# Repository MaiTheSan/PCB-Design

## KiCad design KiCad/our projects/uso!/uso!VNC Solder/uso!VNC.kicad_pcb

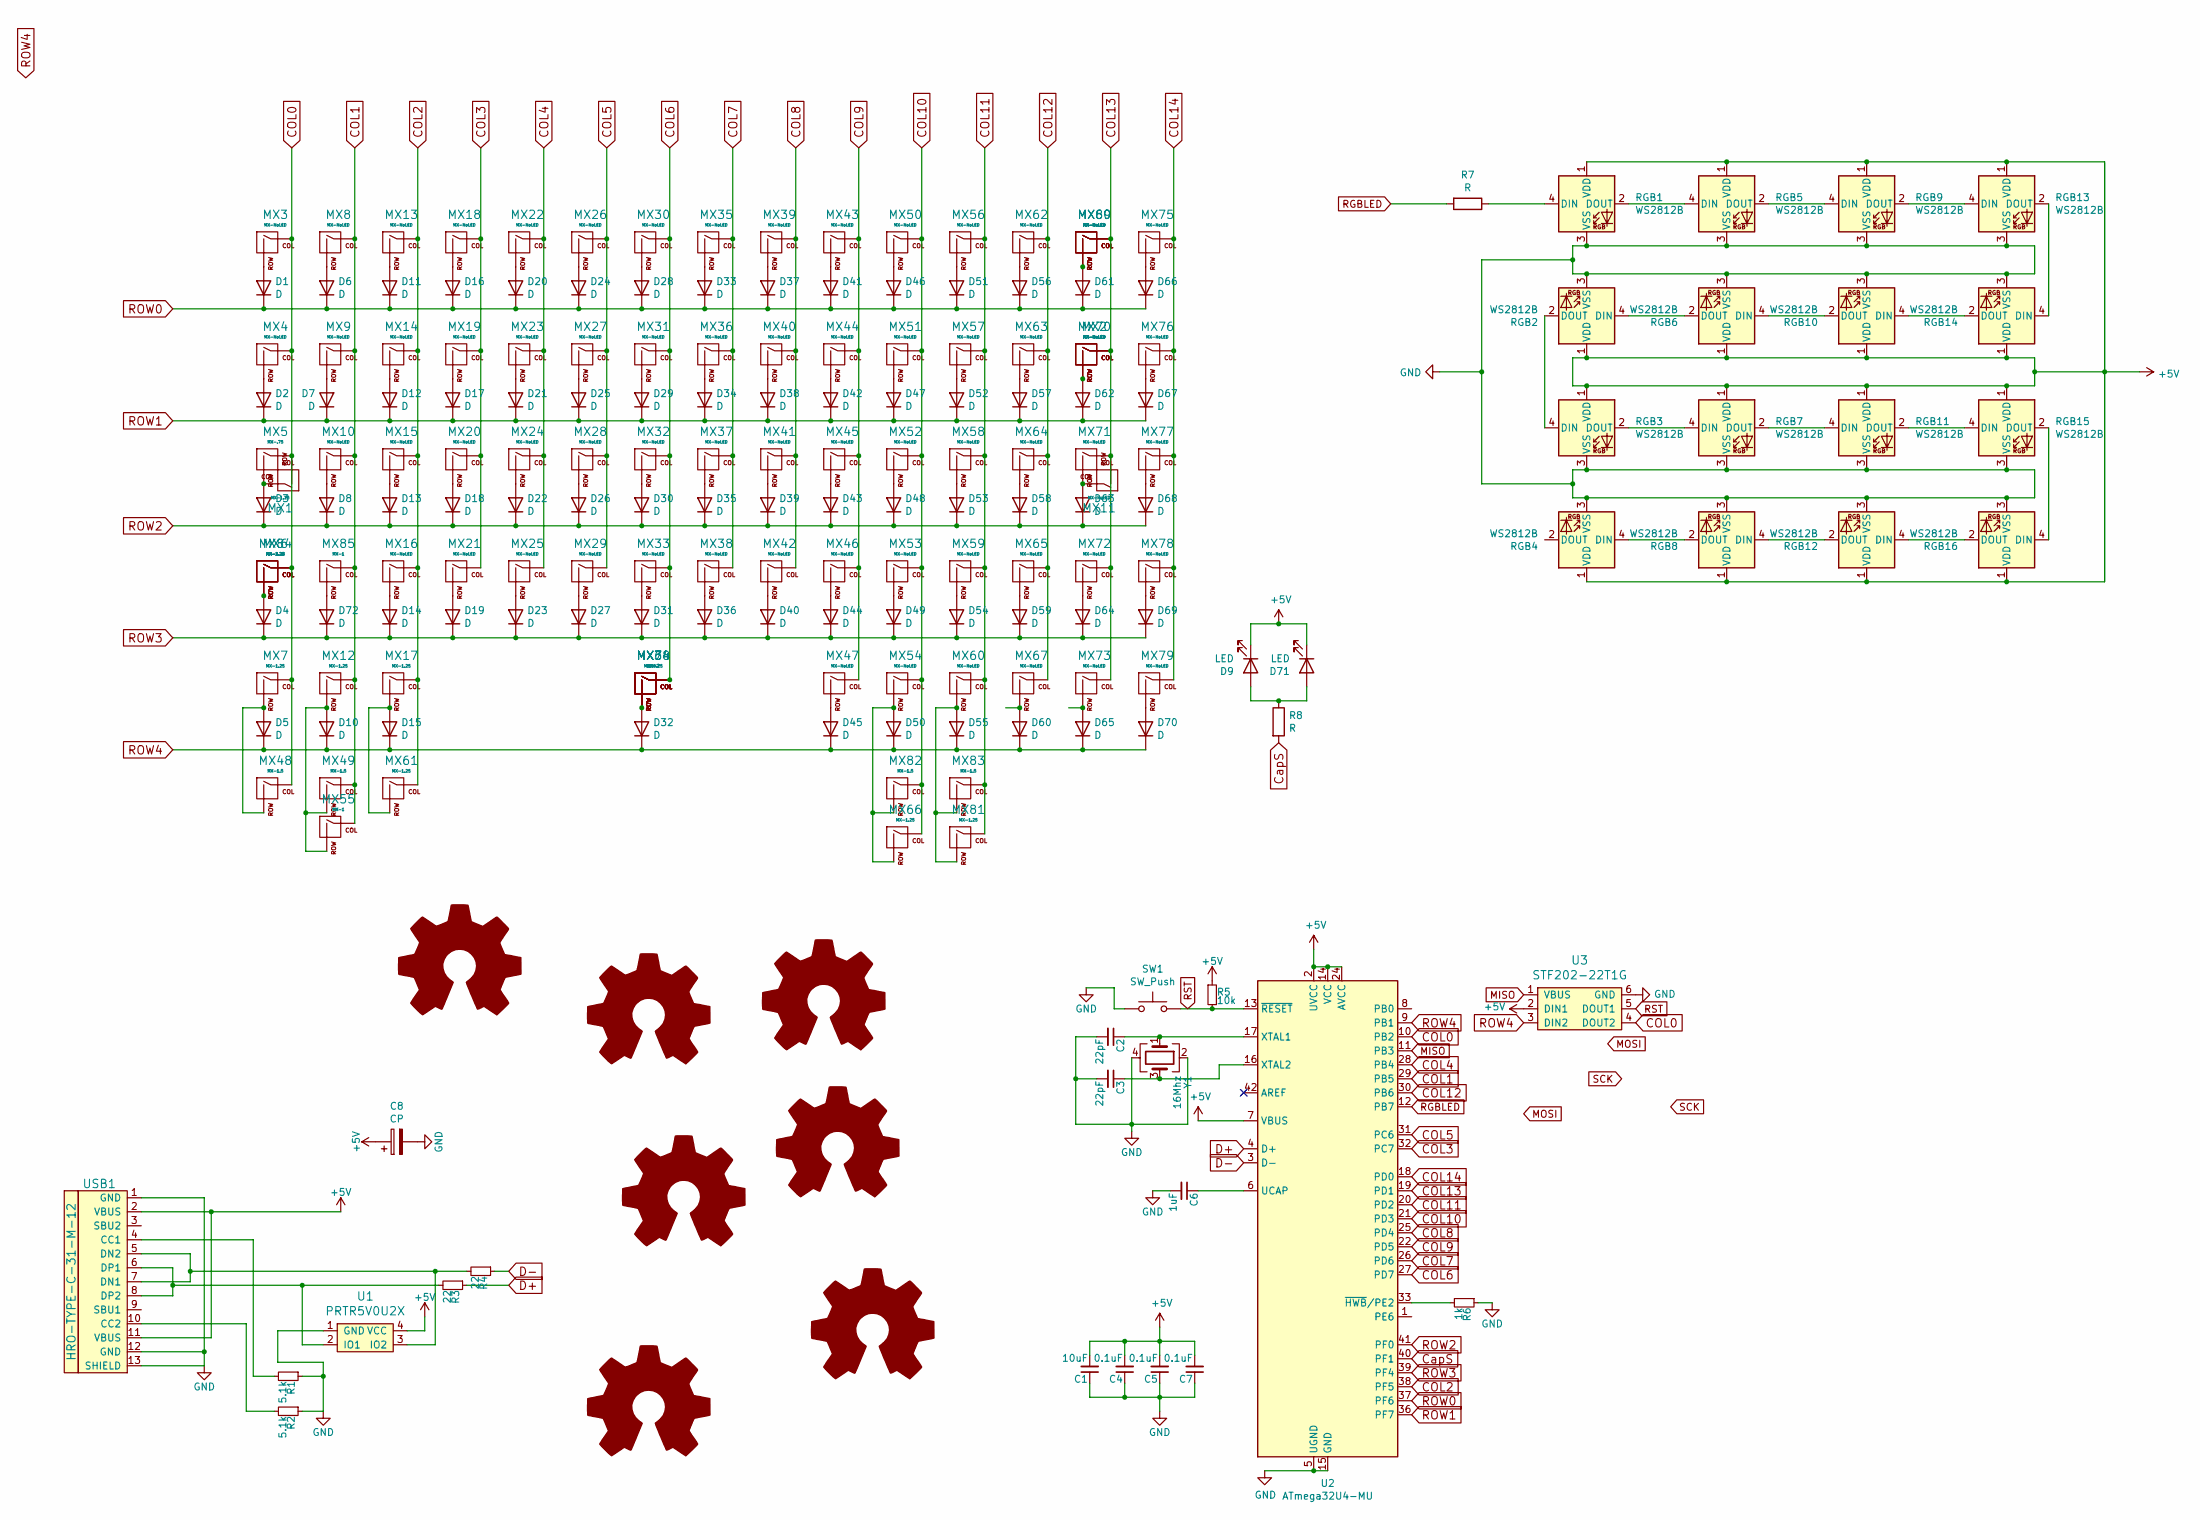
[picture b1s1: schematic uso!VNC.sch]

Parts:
C1: 10uF; C_0603
C2, C3: 22pF; C_0603
C4, C5, C7: 0.1uF; C_0603
C6: 1uF; C_0603
C8: CP; CP_EIA-3216
D1, D2, D3, D4, D5, D6, D7, D8, D10, D11, D12, D13, D14, D15, D16, D17, D18, D19, D20, D21, D22, D23, D24, D25, D26, D27, D28, D29, D30, D31, D32, D33, D34, D35, D36, D37, D38, D39, D40, D41, D42, D43, D44, D45, D46, D47, D48, D49, D50, D51, D52, D53, D54, D55, D56, D57, D58, D59, D60, D61, D62, D63, D64, D65, D66, D67, D68, D69, D70, D72: D; D_SOD-123
D9: LED; MXOnly-LEDONLY-FLIPPED
D71: LED; MXOnly-LEDONLY
LOGO1: Logo_Open_Hardware_Large; sanpjxlogo-PCB-type
LOGO2: Logo_Open_Hardware_Large; mounting-circular
LOGO3, LOGO4, LOGO5, LOGO6, LOGO7: Logo_Open_Hardware_Large; mounting-elipse
MX1, MX7, MX12, MX17, MX61, MX66, MX81, MX84: MX-1.25; MXOnly-1.25U-NoLED
MX2, MX3, MX8, MX9, MX10, MX13, MX14, MX15, MX16, MX18, MX19, MX20, MX21, MX22, MX23, MX24, MX25, MX26, MX27, MX28, MX29, MX30, MX31, MX32, MX33, MX35, MX36, MX37, MX38, MX39, MX40, MX41, MX42, MX43, MX44, MX45, MX46, MX47, MX50, MX51, MX52, MX53, MX54, MX56, MX57, MX58, MX59, MX60, MX62, MX63, MX64, MX67, MX69, MX72, MX73, MX75, MX76, MX77, MX78, MX79: MX-NoLED; MXOnly-1U-NoLED
MX4, MX70: MX-NoLED; MXOnly-1.5U-NoLED
MX5: MX-.75; MXOnly-1.75U-NoLED
MX6: MX-2.25; MXOnly-2.25U-NoLED
MX11: MX-NoLED; MXOnly-ISO-ROTATED-ReversedStabilizers-NoLED
MX34: MX-6.25; MXOnly-6.25U-ReversedStabilizers-NoLED
MX48, MX49, MX82, MX83: MX-1.5; MXOnly-1.5U-NoLED
MX55, MX85: MX-1; MXOnly-1U-NoLED
MX65: MX-NoLED; MXOnly-1.75U-NoLED
MX68, MX74: MX-7; MXOnly-7U-ReversedStabilizers-NoLED
MX71: MX-NoLED; MXOnly-2.25U-NoLED
MX80: MX-NoLED; MXOnly-2U-NoLED
R1, R2: 5.1k; R_0805
R3, R4: 22; R_0805
R5: 10k; R_0805
R6: 1k; R_0805
R7, R8: R; R_0805
RGB1, RGB2, RGB3, RGB4, RGB5, RGB6, RGB7, RGB8, RGB9, RGB10, RGB11, RGB12, RGB13, RGB14, RGB15, RGB16: WS2812B; LED_WS2812B_PLCC4_5.0x5.0mm_P3.2mm
SW1: SW_Push; SKQG-1155865
U1: PRTR5V0U2X; SOT143B
U2: ATmega32U4-MU; QFN-44-1EP_7x7mm_P0.5mm_EP5.2x5.2mm_ThermalVias
U3: STF202-22T1G; vcl65-debuger
USB1: HRO-TYPE-C-31-M-12; HRO-TYPE-C-31-M-12-Assembly
Y1: 16Mhz; Crystal_SMD_3225-4Pin_3.2x2.5mm

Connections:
+5V: C1.2, C4.2, C5.2, C7.2, C8.1, D9.1 (K), D71.1 (K), R5.1, RGB1.1 (VDD), RGB2.1 (VDD), RGB3.1 (VDD), RGB4.1 (VDD), RGB5.1 (VDD), RGB6.1 (VDD), RGB7.1 (VDD), RGB8.1 (VDD), RGB9.1 (VDD), RGB10.1 (VDD), RGB11.1 (VDD), RGB12.1 (VDD), RGB13.1 (VDD), RGB14.1 (VDD), RGB15.1 (VDD), RGB16.1 (VDD), U1.4 (VCC), U2.2 (UVCC), U2.7 (VBUS), U2.14 (VCC), U2.24 (AVCC), U2.34 (VCC), U2.44 (AVCC), U3.2 (DIN1), USB1.2 (VBUS), USB1.11 (VBUS)
COL0: MX1.2 (ROW), MX3.1 (COL), MX4.1 (COL), MX5.1 (COL), MX6.1 (COL), MX7.1 (COL), MX48.1 (COL), MX84.1 (COL), U2.10 (PB2), U3.4 (DOUT2)
COL1: MX8.1 (COL), MX9.1 (COL), MX10.1 (COL), MX12.1 (COL), MX49.1 (COL), MX55.1 (COL), MX85.1 (COL), U2.29 (PB5)
COL2: MX13.1 (COL), MX14.1 (COL), MX15.1 (COL), MX16.1 (COL), MX17.1 (COL), MX61.1 (COL), U2.38 (PF5)
COL3: MX18.1 (COL), MX19.1 (COL), MX20.1 (COL), MX21.1 (COL), U2.32 (PC7)
COL4: MX22.1 (COL), MX23.1 (COL), MX24.1 (COL), MX25.1 (COL), U2.28 (PB4)
COL5: MX26.1 (COL), MX27.1 (COL), MX28.1 (COL), MX29.1 (COL), U2.31 (PC6)
COL6: MX30.1 (COL), MX31.1 (COL), MX32.1 (COL), MX33.1 (COL), MX34.1 (COL), MX68.1 (COL), MX74.1 (COL), U2.27 (PD7)
COL7: MX35.1 (COL), MX36.1 (COL), MX37.1 (COL), MX38.1 (COL), U2.26 (PD6)
COL8: MX39.1 (COL), MX40.1 (COL), MX41.1 (COL), MX42.1 (COL), U2.25 (PD4)
COL9: MX43.1 (COL), MX44.1 (COL), MX45.1 (COL), MX46.1 (COL), MX47.1 (COL), U2.22 (PD5)
COL10: MX50.1 (COL), MX51.1 (COL), MX52.1 (COL), MX53.1 (COL), MX54.1 (COL), MX66.1 (COL), MX82.1 (COL), U2.21 (PD3)
COL11: MX56.1 (COL), MX57.1 (COL), MX58.1 (COL), MX59.1 (COL), MX60.1 (COL), MX81.1 (COL), MX83.1 (COL), U2.20 (PD2)
COL12: MX62.1 (COL), MX63.1 (COL), MX64.1 (COL), MX65.1 (COL), MX67.1 (COL), U2.30 (PB6)
COL13: MX2.1 (COL), MX11.2 (ROW), MX69.1 (COL), MX70.1 (COL), MX71.1 (COL), MX72.1 (COL), MX73.1 (COL), MX80.1 (COL), U2.19 (PD1)
COL14: MX75.1 (COL), MX76.1 (COL), MX77.1 (COL), MX78.1 (COL), MX79.1 (COL), U2.18 (PD0)
CapS: R8.2, U2.40 (PF1)
D+: R3.1, U2.4 (D+)
D-: R4.1, U2.3 (D-)
GND: C1.1, C2.2, C3.2, C4.1, C5.1, C6.2, C7.1, C8.2, R1.1, R2.1, R6.1, RGB1.3 (VSS), RGB2.3 (VSS), RGB3.3 (VSS), RGB4.3 (VSS), RGB5.3 (VSS), RGB6.3 (VSS), RGB7.3 (VSS), RGB8.3 (VSS), RGB9.3 (VSS), RGB10.3 (VSS), RGB11.3 (VSS), RGB12.3 (VSS), RGB13.3 (VSS), RGB14.3 (VSS), RGB15.3 (VSS), RGB16.3 (VSS), SW1.1, U1.1 (GND), U2.5 (UGND), U2.15 (GND), U2.23 (GND), U2.35 (GND), U2.43 (GND), U2.45 (GND), U3.6 (GND), USB1.1 (GND), USB1.12 (GND), USB1.13 (SHIELD), Y1.2, Y1.4
MISO: U2.11 (PB3), U3.1 (VBUS)
unnamed: C2.1, U2.17 (XTAL1), Y1.1
unnamed: C3.1, U2.16 (XTAL2), Y1.3
unnamed: C6.1, U2.6 (UCAP)
unnamed: D1.2 (A), MX3.2 (ROW)
unnamed: D2.2 (A), MX4.2 (ROW)
unnamed: D3.2 (A), MX1.1 (COL), MX5.2 (ROW)
unnamed: D4.2 (A), MX6.2 (ROW), MX84.2 (ROW)
unnamed: D5.2 (A), MX7.2 (ROW), MX48.2 (ROW)
unnamed: D6.2 (A), MX8.2 (ROW)
unnamed: D7.2 (A), MX9.2 (ROW)
unnamed: D8.2 (A), MX10.2 (ROW)
unnamed: D10.2 (A), MX12.2 (ROW), MX49.2 (ROW), MX55.2 (ROW)
unnamed: D11.2 (A), MX13.2 (ROW)
unnamed: D12.2 (A), MX14.2 (ROW)
unnamed: D13.2 (A), MX15.2 (ROW)
unnamed: D14.2 (A), MX16.2 (ROW)
unnamed: D15.2 (A), MX17.2 (ROW), MX61.2 (ROW)
unnamed: D16.2 (A), MX18.2 (ROW)
unnamed: D17.2 (A), MX19.2 (ROW)
unnamed: D18.2 (A), MX20.2 (ROW)
unnamed: D19.2 (A), MX21.2 (ROW)
unnamed: D20.2 (A), MX22.2 (ROW)
unnamed: D21.2 (A), MX23.2 (ROW)
unnamed: D22.2 (A), MX24.2 (ROW)
unnamed: D23.2 (A), MX25.2 (ROW)
unnamed: D24.2 (A), MX26.2 (ROW)
unnamed: D25.2 (A), MX27.2 (ROW)
unnamed: D26.2 (A), MX28.2 (ROW)
unnamed: D27.2 (A), MX29.2 (ROW)
unnamed: D28.2 (A), MX30.2 (ROW)
unnamed: D29.2 (A), MX31.2 (ROW)
unnamed: D30.2 (A), MX32.2 (ROW)
unnamed: D31.2 (A), MX33.2 (ROW)
unnamed: D32.2 (A), MX34.2 (ROW), MX68.2 (ROW), MX74.2 (ROW)
unnamed: D33.2 (A), MX35.2 (ROW)
unnamed: D34.2 (A), MX36.2 (ROW)
unnamed: D35.2 (A), MX37.2 (ROW)
unnamed: D36.2 (A), MX38.2 (ROW)
unnamed: D37.2 (A), MX39.2 (ROW)
unnamed: D38.2 (A), MX40.2 (ROW)
unnamed: D39.2 (A), MX41.2 (ROW)
unnamed: D40.2 (A), MX42.2 (ROW)
unnamed: D41.2 (A), MX43.2 (ROW)
unnamed: D42.2 (A), MX44.2 (ROW)
unnamed: D43.2 (A), MX45.2 (ROW)
unnamed: D44.2 (A), MX46.2 (ROW)
unnamed: D45.2 (A), MX47.2 (ROW)
unnamed: D46.2 (A), MX50.2 (ROW)
unnamed: D47.2 (A), MX51.2 (ROW)
unnamed: D48.2 (A), MX52.2 (ROW)
unnamed: D49.2 (A), MX53.2 (ROW)
unnamed: D50.2 (A), MX54.2 (ROW), MX66.2 (ROW), MX82.2 (ROW)
unnamed: D51.2 (A), MX56.2 (ROW)
unnamed: D52.2 (A), MX57.2 (ROW)
unnamed: D53.2 (A), MX58.2 (ROW)
unnamed: D54.2 (A), MX59.2 (ROW)
unnamed: D55.2 (A), MX60.2 (ROW), MX81.2 (ROW), MX83.2 (ROW)
unnamed: D56.2 (A), MX62.2 (ROW)
unnamed: D57.2 (A), MX63.2 (ROW)
unnamed: D58.2 (A), MX64.2 (ROW)
unnamed: D59.2 (A), MX65.2 (ROW)
unnamed: D60.2 (A), MX67.2 (ROW)
unnamed: D61.2 (A), MX69.2 (ROW), MX80.2 (ROW)
unnamed: D62.2 (A), MX2.2 (ROW), MX70.2 (ROW)
unnamed: D63.2 (A), MX11.1 (COL), MX71.2 (ROW)
unnamed: D64.2 (A), MX72.2 (ROW)
unnamed: D65.2 (A), MX73.2 (ROW)
unnamed: D66.2 (A), MX75.2 (ROW)
unnamed: D67.2 (A), MX76.2 (ROW)
unnamed: D68.2 (A), MX77.2 (ROW)
unnamed: D69.2 (A), MX78.2 (ROW)
unnamed: D70.2 (A), MX79.2 (ROW)
unnamed: D9.2 (A), D71.2 (A), R8.1
unnamed: D72.2 (A), MX85.2 (ROW)
unnamed: R1.2, USB1.4 (CC1)
unnamed: R2.2, USB1.10 (CC2)
unnamed: R3.2, U1.2 (IO1), USB1.6 (DP1), USB1.8 (DP2)
unnamed: R4.2, U1.3 (IO2), USB1.5 (DN2), USB1.7 (DN1)
unnamed: R6.2, U2.33 (~HWB~/PE2)
unnamed: R7.1, RGB1.4 (DIN)
unnamed: RGB1.2 (DOUT), RGB5.4 (DIN)
unnamed: RGB2.2 (DOUT), RGB3.4 (DIN)
unnamed: RGB2.4 (DIN), RGB6.2 (DOUT)
unnamed: RGB3.2 (DOUT), RGB7.4 (DIN)
unnamed: RGB4.4 (DIN), RGB8.2 (DOUT)
unnamed: RGB5.2 (DOUT), RGB9.4 (DIN)
unnamed: RGB6.4 (DIN), RGB10.2 (DOUT)
unnamed: RGB10.4 (DIN), RGB14.2 (DOUT)
unnamed: RGB11.2 (DOUT), RGB15.4 (DIN)
unnamed: RGB7.2 (DOUT), RGB11.4 (DIN)
unnamed: RGB8.4 (DIN), RGB12.2 (DOUT)
unnamed: RGB12.4 (DIN), RGB16.2 (DOUT)
unnamed: RGB13.2 (DOUT), RGB14.4 (DIN)
unnamed: RGB9.2 (DOUT), RGB13.4 (DIN)
unnamed: RGB15.2 (DOUT), RGB16.4 (DIN)
RGBLED: R7.2, U2.12 (PB7)
ROW0: D1.1 (K), D6.1 (K), D11.1 (K), D16.1 (K), D20.1 (K), D24.1 (K), D28.1 (K), D33.1 (K), D37.1 (K), D41.1 (K), D46.1 (K), D51.1 (K), D56.1 (K), D61.1 (K), D66.1 (K), U2.37 (PF6)
ROW1: D2.1 (K), D7.1 (K), D12.1 (K), D17.1 (K), D21.1 (K), D25.1 (K), D29.1 (K), D34.1 (K), D38.1 (K), D42.1 (K), D47.1 (K), D52.1 (K), D57.1 (K), D62.1 (K), D67.1 (K), U2.36 (PF7)
ROW2: D3.1 (K), D8.1 (K), D13.1 (K), D18.1 (K), D22.1 (K), D26.1 (K), D30.1 (K), D35.1 (K), D39.1 (K), D43.1 (K), D48.1 (K), D53.1 (K), D58.1 (K), D63.1 (K), D68.1 (K), U2.41 (PF0)
ROW3: D4.1 (K), D14.1 (K), D19.1 (K), D23.1 (K), D27.1 (K), D31.1 (K), D36.1 (K), D40.1 (K), D44.1 (K), D49.1 (K), D54.1 (K), D59.1 (K), D64.1 (K), D69.1 (K), D72.1 (K), U2.39 (PF4)
ROW4: D5.1 (K), D10.1 (K), D15.1 (K), D32.1 (K), D45.1 (K), D50.1 (K), D55.1 (K), D60.1 (K), D65.1 (K), D70.1 (K), U2.9 (PB1), U3.3 (DIN2)
RST: R5.2, SW1.2, U2.13 (~RESET), U3.5 (DOUT1)

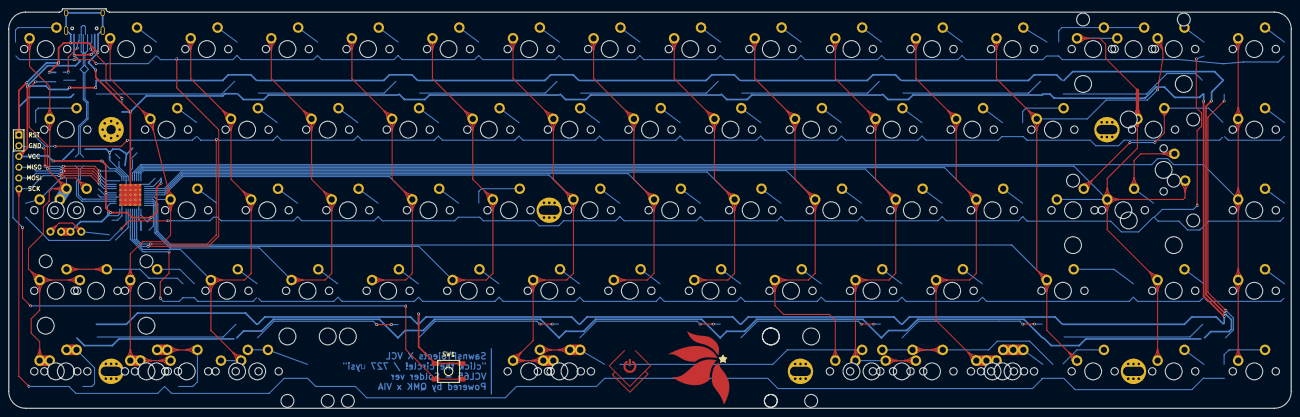
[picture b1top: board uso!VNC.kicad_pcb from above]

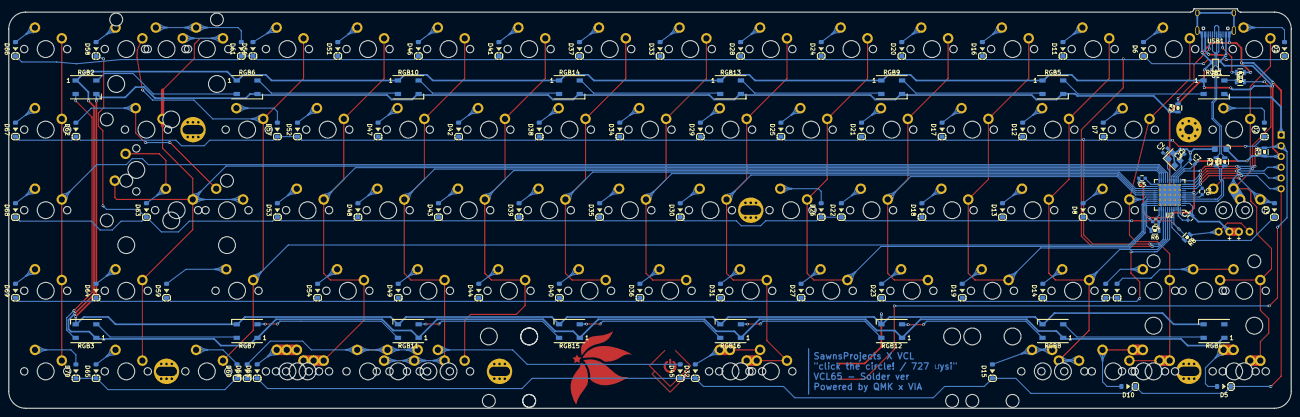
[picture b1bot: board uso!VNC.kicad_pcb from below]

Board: 2 copper layers, 303.2 x 94.5 mm, 202 parts (106 on the bottom side), 123 nets.

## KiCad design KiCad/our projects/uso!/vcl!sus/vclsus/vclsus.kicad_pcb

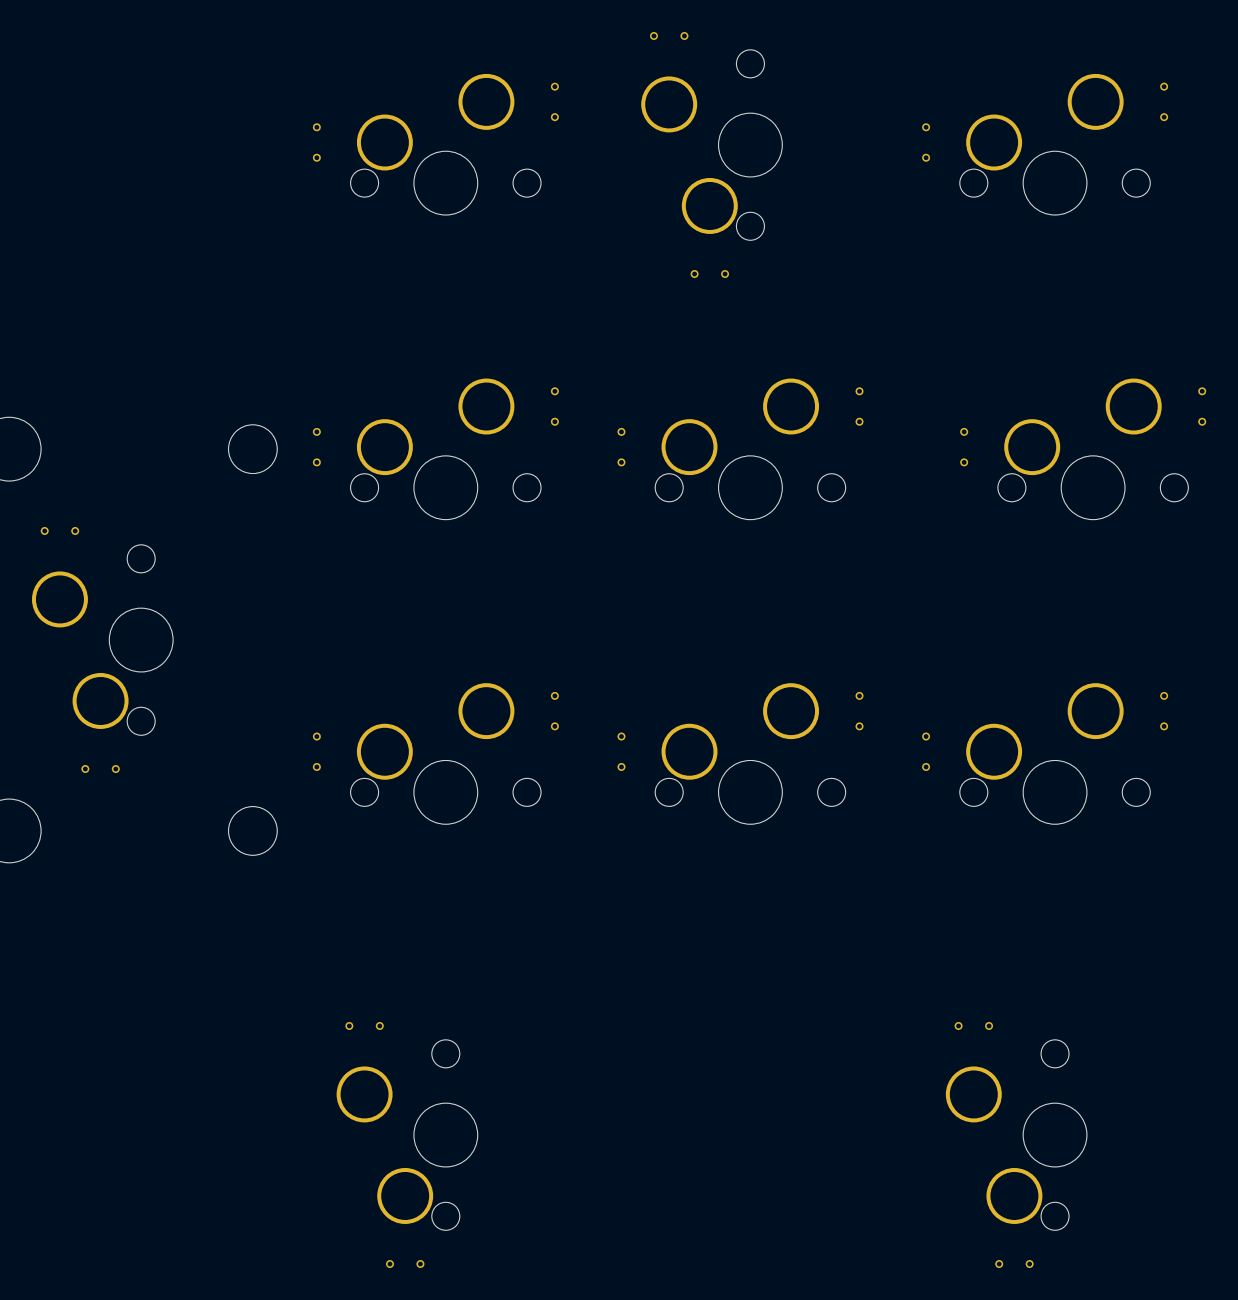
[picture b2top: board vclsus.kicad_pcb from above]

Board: 2 copper layers, 12 parts (0 on the bottom side), 3 nets, no tracks yet.

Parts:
MX1: 2U; MXOnly-2U-Hotswap-ReversedStabilizers-Sawns
MX2, MX3, MX4, MX7, MX8, MX9, MX11: 1U; MXOnly-1U-Hotswap-Sawns
MX5, MX6, MX10, MX12: 1.25U; MXOnly-1.25U-Hotswap-Sawns

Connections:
unnamed: MX2.1, MX3.1, MX4.1, MX5.1
unnamed: MX6.1, MX7.1, MX8.1
unnamed: MX9.1, MX10.1, MX11.1, MX12.1

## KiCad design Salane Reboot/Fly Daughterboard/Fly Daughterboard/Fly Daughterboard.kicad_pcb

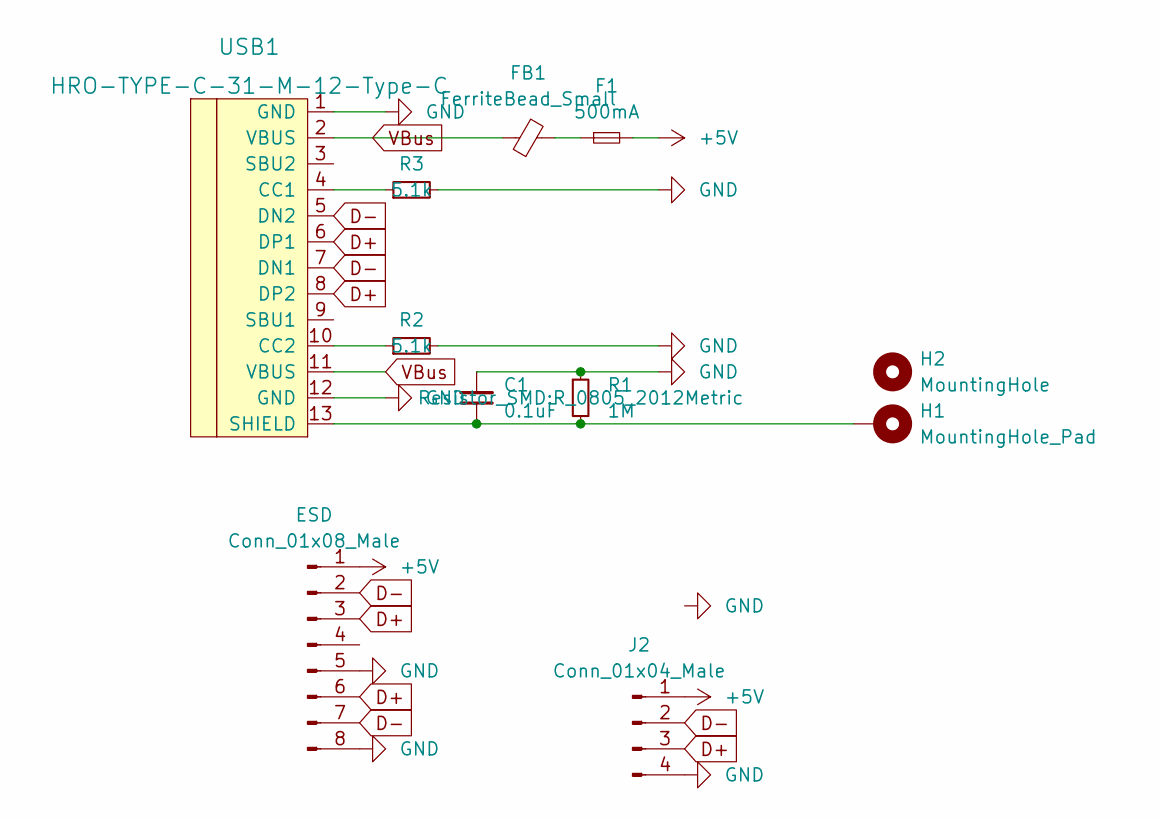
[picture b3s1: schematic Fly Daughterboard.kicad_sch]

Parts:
C1: 0.1uF; C_0805_2012Metric
ESD: Conn_01x08_Male; uQFN8
F1: 500mA; Fuse_0603_1608Metric
FB1: FerriteBead_Small; Fuse_0603_1608Metric
H1: MountingHole_Pad; MountingHole_2.2mm_M2_ISO7380_Pad
H2: MountingHole; MountingHole_2.2mm_M2_ISO7380_Pad
J2: Conn_01x04_Male; JST-SR-4-mini
R1: 1M; R_0805_2012Metric
R2, R3: 5.1k; R_0402_1005Metric
USB1: HRO-TYPE-C-31-M-12-Type-C; HRO-TYPE-C-31-M-12-Assembly

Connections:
+5V: ESD.1, F1.2, J2.1; also elsewhere on the board
D+: ESD.3, ESD.6, J2.3, USB1.6 (DP1), USB1.8 (DP2); also elsewhere on the board
D-: ESD.2, ESD.7, J2.2, USB1.5 (DN2), USB1.7 (DN1); also elsewhere on the board
GND: C1.2, ESD.5, ESD.8, J2.4, R1.1, R2.2, R3.2, USB1.1 (GND), USB1.12 (GND); also elsewhere on the board
unnamed: C1.1, H1.1, R1.2, USB1.13 (SHIELD)
unnamed: F1.1, FB1.2
unnamed: R2.1, USB1.10 (CC2)
unnamed: R3.1, USB1.4 (CC1)
VBus: FB1.1, USB1.2 (VBUS), USB1.11 (VBUS)

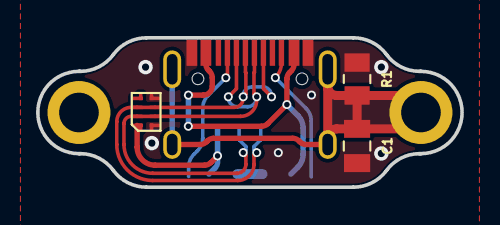
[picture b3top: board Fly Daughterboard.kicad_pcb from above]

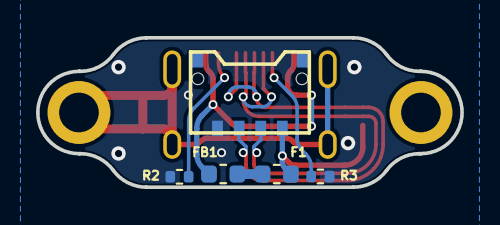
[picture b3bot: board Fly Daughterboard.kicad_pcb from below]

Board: 2 copper layers, 23.6 x 8.3 mm, 11 parts (5 on the bottom side), 9 nets.

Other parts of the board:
ESD1: Conn_01x08_Male; uQFN8

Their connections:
+5V: ESD1.1; also elsewhere on the board
D+: ESD1.3, ESD1.6; also elsewhere on the board
D-: ESD1.2, ESD1.7; also elsewhere on the board
GND: ESD1.5, ESD1.8; also elsewhere on the board

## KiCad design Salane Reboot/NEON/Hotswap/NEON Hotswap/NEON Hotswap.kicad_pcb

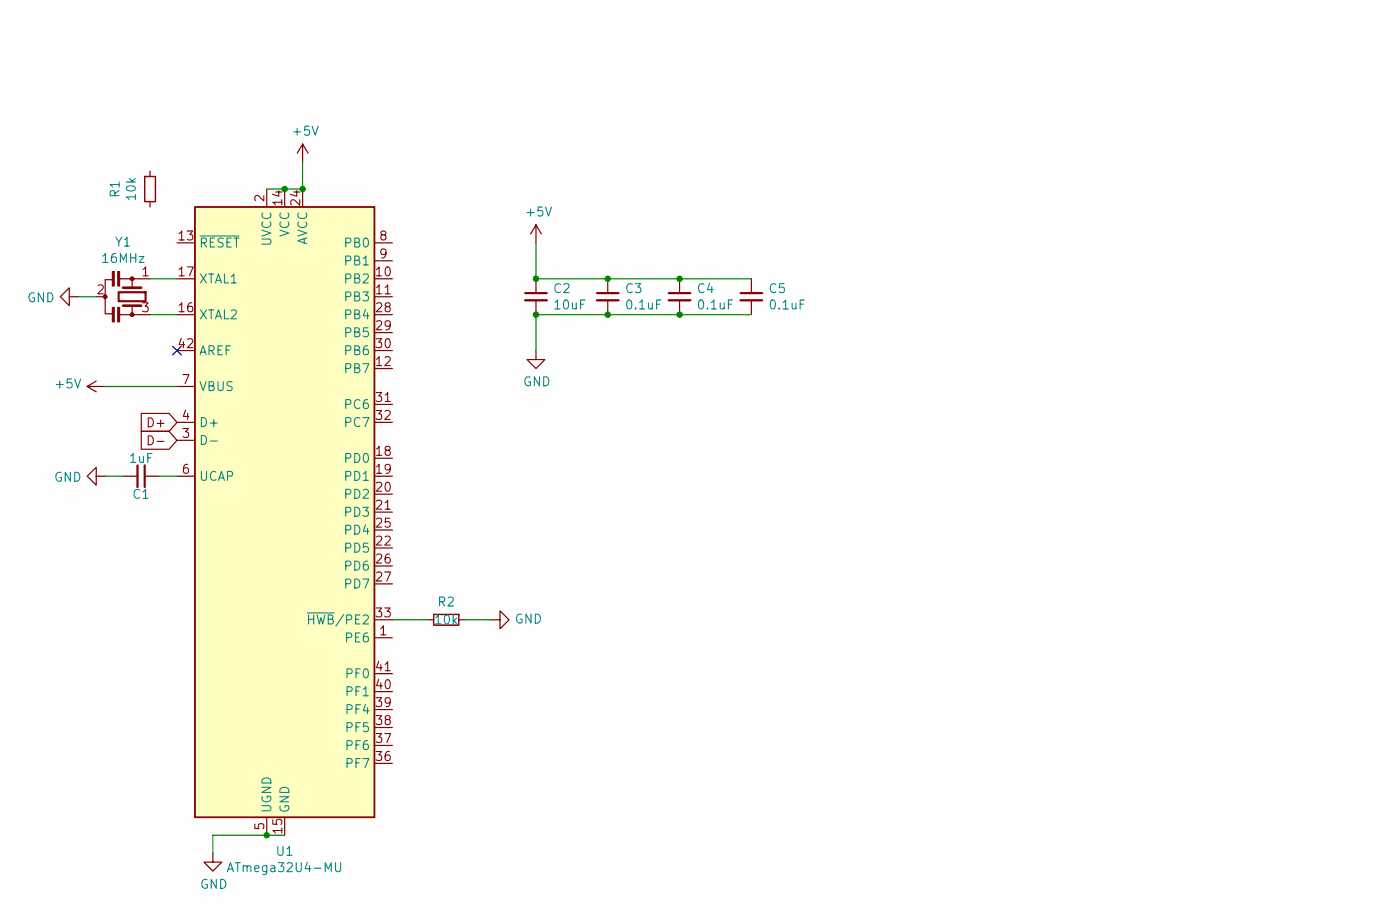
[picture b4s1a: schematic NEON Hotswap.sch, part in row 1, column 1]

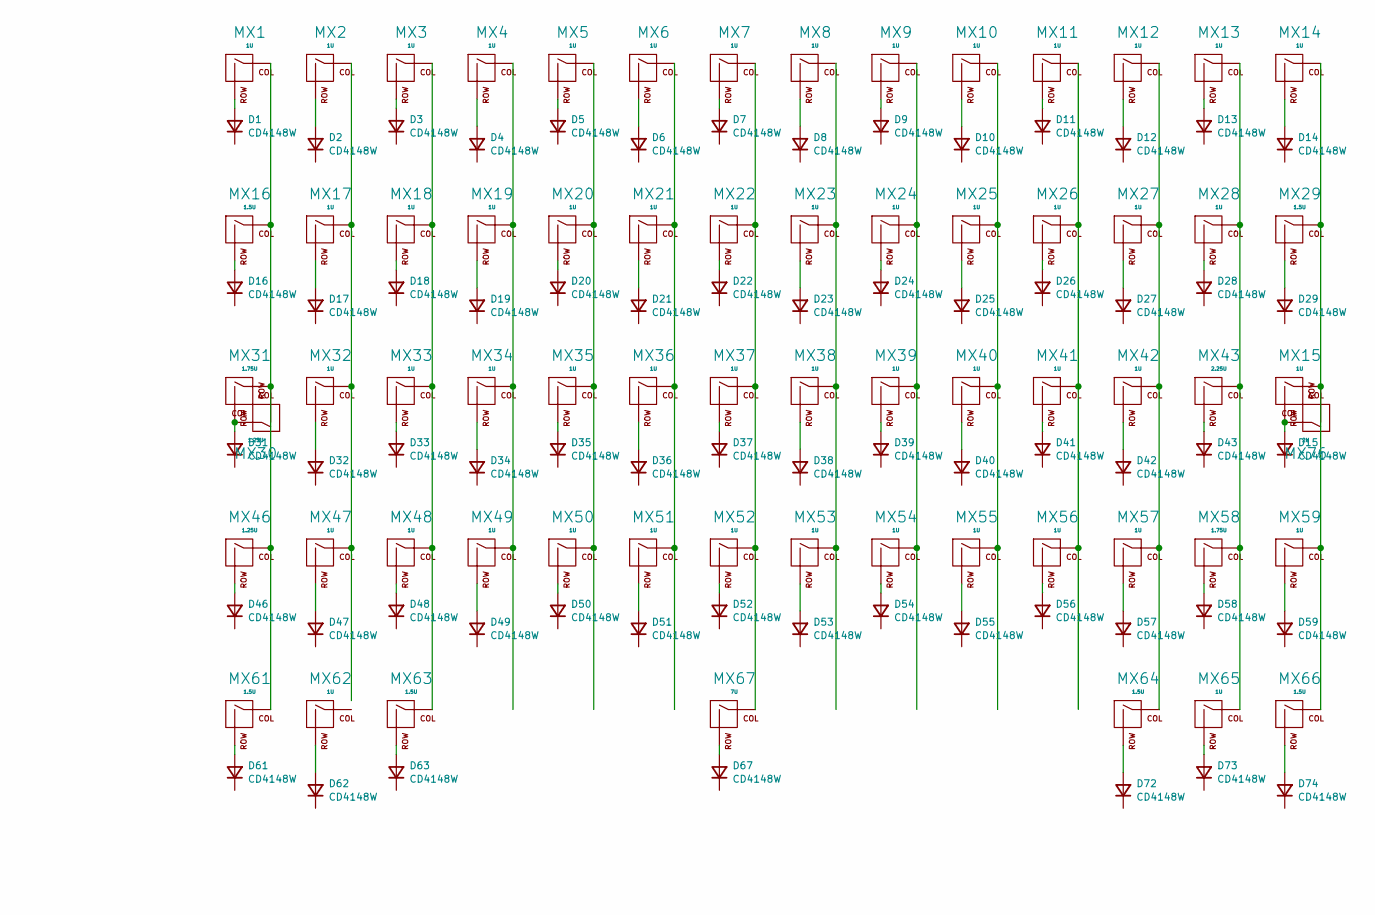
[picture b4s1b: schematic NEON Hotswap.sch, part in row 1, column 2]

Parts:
C1: 1uF; C_0402
C2: 10uF; C_0402
C3, C4, C5: 0.1uF; C_0402
D1, D2, D3, D4, D5, D6, D7, D8, D9, D10, D11, D12, D13, D14, D15, D16, D17, D18, D19, D20, D21, D22, D23, D24, D25, D26, D27, D28, D29, D31, D32, D33, D34, D35, D36, D37, D38, D39, D40, D41, D42, D43, D46, D47, D48, D49, D50, D51, D52, D53, D54, D55, D56, D57, D58, D59, D61, D62, D63, D67, D72, D73, D74: CD4148W; DIODE_1206_SawnsProjects
MX1, MX2, MX3, MX4, MX5, MX6, MX7, MX8, MX9, MX10, MX11, MX12, MX13, MX14, MX15, MX17, MX18, MX19, MX20, MX21, MX22, MX23, MX24, MX25, MX26, MX27, MX28, MX32, MX33, MX34, MX35, MX36, MX37, MX38, MX39, MX40, MX41, MX42, MX47, MX48, MX49, MX50, MX51, MX52, MX53, MX54, MX55, MX56, MX57, MX59, MX62, MX65: 1U; MXOnly-1U-Hotswap-Sawns
MX16, MX29, MX61, MX63, MX64, MX66: 1.5U; MXOnly-1.5U-Hotswap-Sawns
MX30, MX46: 1.25U; MXOnly-1.25U-Hotswap-Sawns
MX31, MX58: 1.75U; MXOnly-1.75U-Hotswap-Sawns
MX43: 2.25U; MXOnly-2.25U-Hotswap-ReversedStabilizers-Sawns
MX67: 7U; MXOnly-7U-Hotswap-Sawns
MX76: 2U; MXOnly-2U-Hotswap-Sawns
R1, R2: 10k
U1: ATmega32U4-MU; QFN-44-1EP_7x7mm_P0.5mm_EP5.2x5.2mm_ThermalVias
Y1: 16MHz; Resonator_SMD_muRata_CSTxExxV-3Pin_3.0x1.1mm

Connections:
+5V: C2.1, C3.1, C4.1, C5.1, U1.2 (UVCC), U1.7 (VBUS), U1.14 (VCC), U1.24 (AVCC), U1.34 (VCC), U1.44 (AVCC)
D+: U1.4 (D+)
D-: U1.3 (D-)
GND: C1.2, C2.2, C3.2, C4.2, C5.2, R2.1, U1.5 (UGND), U1.15 (GND), U1.23 (GND), U1.35 (GND), U1.43 (GND), U1.45 (GND), Y1.2
unnamed: C1.1, U1.6 (UCAP)
unnamed: D1.2 (A), MX1.2 (ROW)
unnamed: D2.2 (A), MX2.2 (ROW)
unnamed: D3.2 (A), MX3.2 (ROW)
unnamed: D4.2 (A), MX4.2 (ROW)
unnamed: D5.2 (A), MX5.2 (ROW)
unnamed: D6.2 (A), MX6.2 (ROW)
unnamed: D7.2 (A), MX7.2 (ROW)
unnamed: D8.2 (A), MX8.2 (ROW)
unnamed: D9.2 (A), MX9.2 (ROW)
unnamed: D10.2 (A), MX10.2 (ROW)
unnamed: D11.2 (A), MX11.2 (ROW)
unnamed: D12.2 (A), MX12.2 (ROW)
unnamed: D13.2 (A), MX13.2 (ROW)
unnamed: D14.2 (A), MX14.2 (ROW)
unnamed: D15.2 (A), MX15.2 (ROW), MX76.1 (COL)
unnamed: D16.2 (A), MX16.2 (ROW)
unnamed: D17.2 (A), MX17.2 (ROW)
unnamed: D18.2 (A), MX18.2 (ROW)
unnamed: D19.2 (A), MX19.2 (ROW)
unnamed: D20.2 (A), MX20.2 (ROW)
unnamed: D21.2 (A), MX21.2 (ROW)
unnamed: D22.2 (A), MX22.2 (ROW)
unnamed: D23.2 (A), MX23.2 (ROW)
unnamed: D24.2 (A), MX24.2 (ROW)
unnamed: D25.2 (A), MX25.2 (ROW)
unnamed: D26.2 (A), MX26.2 (ROW)
unnamed: D27.2 (A), MX27.2 (ROW)
unnamed: D28.2 (A), MX28.2 (ROW)
unnamed: D29.2 (A), MX29.2 (ROW)
unnamed: D31.2 (A), MX30.1 (COL), MX31.2 (ROW)
unnamed: D32.2 (A), MX32.2 (ROW)
unnamed: D33.2 (A), MX33.2 (ROW)
unnamed: D34.2 (A), MX34.2 (ROW)
unnamed: D35.2 (A), MX35.2 (ROW)
unnamed: D36.2 (A), MX36.2 (ROW)
unnamed: D37.2 (A), MX37.2 (ROW)
unnamed: D38.2 (A), MX38.2 (ROW)
unnamed: D39.2 (A), MX39.2 (ROW)
unnamed: D40.2 (A), MX40.2 (ROW)
unnamed: D41.2 (A), MX41.2 (ROW)
unnamed: D42.2 (A), MX42.2 (ROW)
unnamed: D43.2 (A), MX43.2 (ROW)
unnamed: D46.2 (A), MX46.2 (ROW)
unnamed: D47.2 (A), MX47.2 (ROW)
unnamed: D48.2 (A), MX48.2 (ROW)
unnamed: D49.2 (A), MX49.2 (ROW)
unnamed: D50.2 (A), MX50.2 (ROW)
unnamed: D51.2 (A), MX51.2 (ROW)
unnamed: D52.2 (A), MX52.2 (ROW)
unnamed: D53.2 (A), MX53.2 (ROW)
unnamed: D54.2 (A), MX54.2 (ROW)
unnamed: D55.2 (A), MX55.2 (ROW)
unnamed: D56.2 (A), MX56.2 (ROW)
unnamed: D57.2 (A), MX57.2 (ROW)
unnamed: D58.2 (A), MX58.2 (ROW)
unnamed: D59.2 (A), MX59.2 (ROW)
unnamed: D61.2 (A), MX61.2 (ROW)
unnamed: D62.2 (A), MX62.2 (ROW)
unnamed: D63.2 (A), MX63.2 (ROW)
unnamed: D67.2 (A), MX67.2 (ROW)
unnamed: D72.2 (A), MX64.2 (ROW)
unnamed: D73.2 (A), MX65.2 (ROW)
unnamed: D74.2 (A), MX66.2 (ROW)
unnamed: MX1.1 (COL), MX16.1 (COL), MX30.2 (ROW), MX31.1 (COL), MX46.1 (COL), MX61.1 (COL)
unnamed: MX10.1 (COL), MX25.1 (COL), MX40.1 (COL), MX55.1 (COL)
unnamed: MX11.1 (COL), MX26.1 (COL), MX41.1 (COL), MX56.1 (COL)
unnamed: MX12.1 (COL), MX27.1 (COL), MX42.1 (COL), MX57.1 (COL), MX64.1 (COL)
unnamed: MX13.1 (COL), MX28.1 (COL), MX43.1 (COL), MX58.1 (COL), MX65.1 (COL)
unnamed: MX14.1 (COL), MX15.1 (COL), MX29.1 (COL), MX59.1 (COL), MX66.1 (COL), MX76.2 (ROW)
unnamed: MX2.1 (COL), MX17.1 (COL), MX32.1 (COL), MX47.1 (COL)
unnamed: MX3.1 (COL), MX18.1 (COL), MX33.1 (COL), MX48.1 (COL), MX63.1 (COL)
unnamed: MX4.1 (COL), MX19.1 (COL), MX34.1 (COL), MX49.1 (COL)
unnamed: MX5.1 (COL), MX20.1 (COL), MX35.1 (COL), MX50.1 (COL)
unnamed: MX6.1 (COL), MX21.1 (COL), MX36.1 (COL), MX51.1 (COL)
unnamed: MX7.1 (COL), MX22.1 (COL), MX37.1 (COL), MX52.1 (COL), MX67.1 (COL)
unnamed: MX8.1 (COL), MX23.1 (COL), MX38.1 (COL), MX53.1 (COL)
unnamed: MX9.1 (COL), MX24.1 (COL), MX39.1 (COL), MX54.1 (COL)
unnamed: R2.2, U1.33 (~HWB~/PE2)
unnamed: U1.16 (XTAL2), Y1.3
unnamed: U1.17 (XTAL1), Y1.1

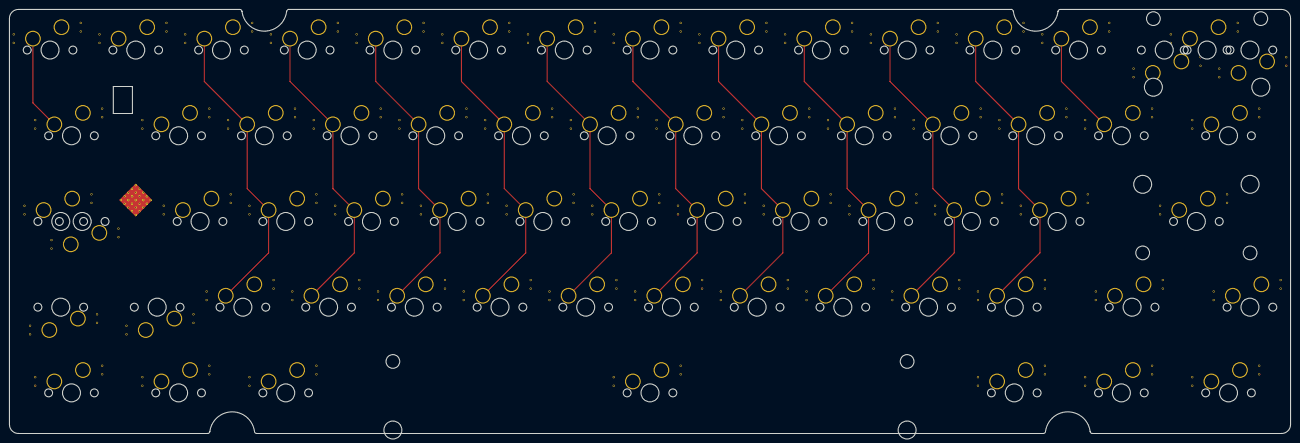
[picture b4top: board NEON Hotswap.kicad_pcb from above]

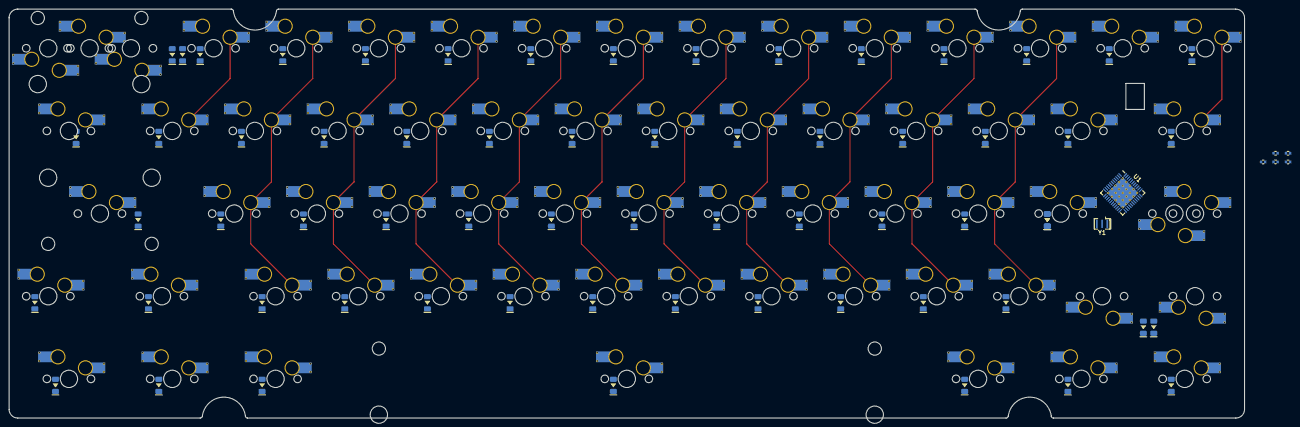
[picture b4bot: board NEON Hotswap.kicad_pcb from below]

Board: 2 copper layers, 284.8 x 94.3 mm, 135 parts (70 on the bottom side), 82 nets.
